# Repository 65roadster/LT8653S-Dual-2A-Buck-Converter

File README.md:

# LT8653S Dual 2A Buck Converter

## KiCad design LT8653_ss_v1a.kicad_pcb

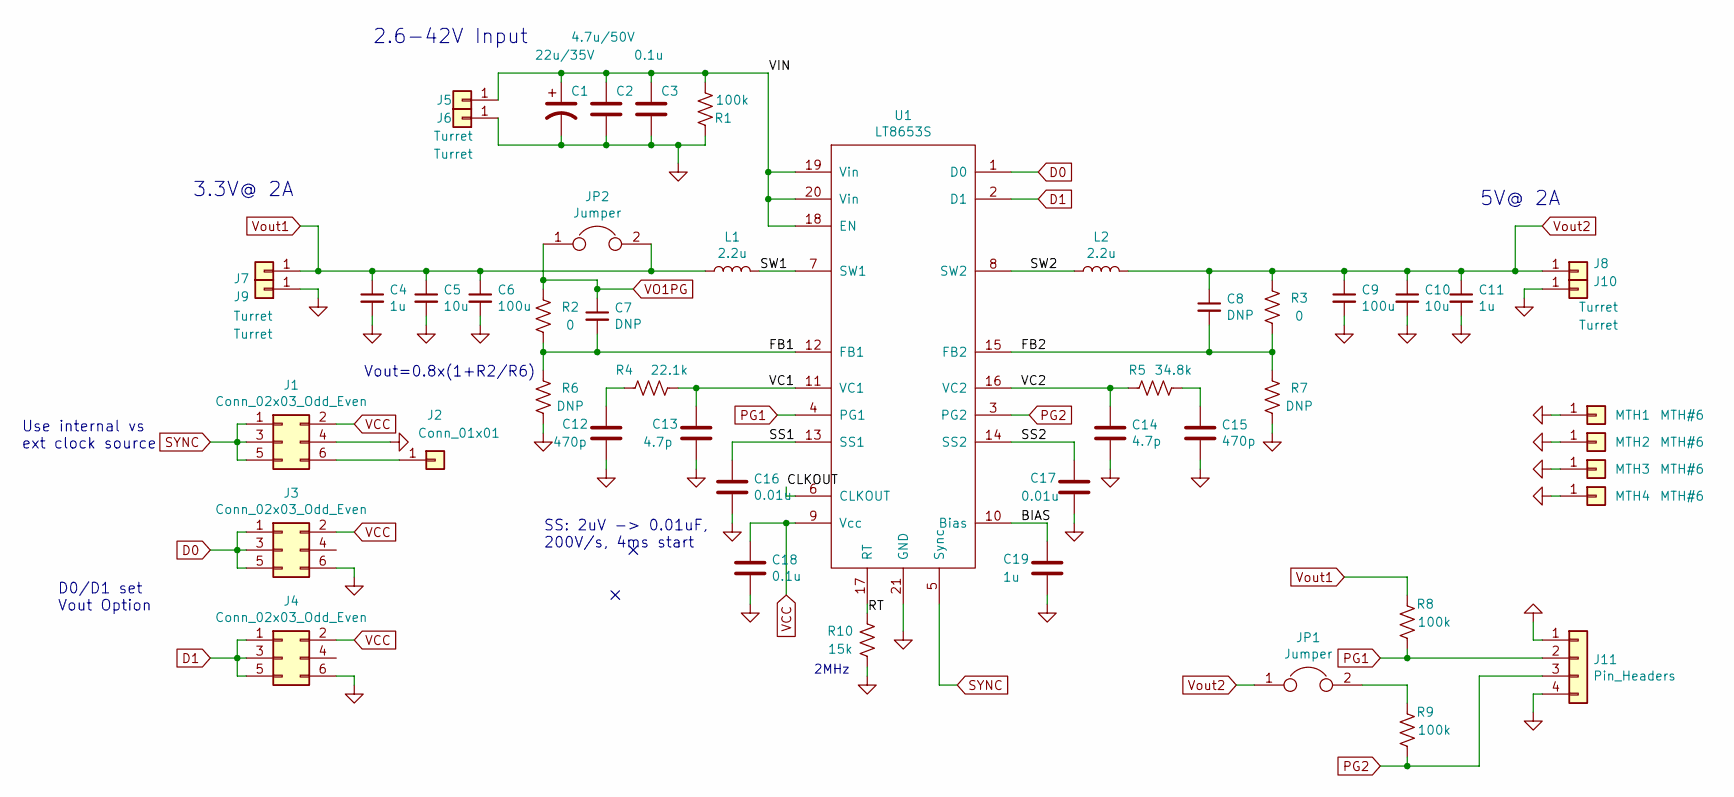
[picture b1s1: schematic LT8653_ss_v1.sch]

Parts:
C1: 22u/35V; CP_Elec_4x4.5
C2: 4.7u/50V; C_0603_HandSoldering
C3, C18: 0.1u; C_0603_HandSoldering
C4, C11, C19: 1u; C_0603_HandSoldering
C5, C10: 10u; C_0603_HandSoldering
C6, C9: 100u; C_1210_HandSoldering
C7, C8: DNP; C_0603_HandSoldering
C12, C15: 470p; C_0603_HandSoldering
C13, C14: 4.7p; C_0603_HandSoldering
C16, C17: 0.01u; C_0603_HandSoldering
J1, J3, J4: Conn_02x03_Odd_Even; Pin_Header_Straight_2x03_Pitch2.54mm
J2: Conn_01x01; Pin_Header_Straight_1x02_Pitch2.54mm
J5, J6, J7, J8, J9, J10: Turret; Pin-MILMAX_2501-2-00-80-00-00-07-0
J11: Pin_Headers; Pin_Header_Straight_1x04_Pitch2.54mm
JP1: Jumper; Jumper_0.3
JP2: Jumper; Jumper_0.6
L1, L2: 2.2u; Inductor_Coilcraft_XFL4020-222ME
MTH1, MTH2, MTH3, MTH4: MTH#6; Mount-Hole-#6
R1, R8, R9: 100k; R_0603_HandSoldering
R2, R3: 0; R_0603_HandSoldering
R4: 22.1k; R_0603_HandSoldering
R5: 34.8k; R_0603_HandSoldering
R6, R7: DNP; R_0603_HandSoldering
R10: 15k; R_0603_HandSoldering
U1: LT8653S; LinearTech-LT-LQFN-20-4mmx3mm

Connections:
/BIAS: C19.1, U1.10 (Bias)
/FB1: C7.2, R2.2, R6.1, U1.12 (FB1)
/FB2: C8.2, R3.2, R7.1, U1.15 (FB2)
/RT: R10.2, U1.17 (RT)
/SS1: C16.1, U1.13 (SS1)
/SS2: C17.1, U1.14 (SS2)
/SW1: L1.2, U1.7 (SW1)
/SW2: L2.1, U1.8 (SW2)
/VC1: C13.1, R4.2, U1.11 (VC1)
/VC2: C14.1, R5.1, U1.16 (VC2)
/VIN: C1.1, C2.1, C3.1, J5.1, R1.2, U1.18 (EN), U1.19 (Vin), U1.20 (Vin)
D0: J3.1, J3.3, J3.5, U1.1 (D0)
D1: J4.1, J4.3, J4.5, U1.2 (D1)
GND: C1.2, C2.2, C3.2, C4.2, C5.2, C6.2, C9.2, C10.2, C11.2, C12.2, C13.2, C14.2, C15.2, C16.2, C17.2, C18.2, C19.2, J1.4, J3.6, J4.6, J6.1, J9.1, J10.1, J11.1, J11.4, MTH1.1, MTH2.1, MTH3.1, MTH4.1, R1.1, R6.2, R7.2, R10.1, U1.21 (GND)
unnamed: C12.1, R4.1
unnamed: C15.1, R5.2
unnamed: J1.6, J2.1
unnamed: JP1.2, R9.1
PG1: J11.2, R8.2, U1.4 (PG1)
PG2: J11.3, R9.2, U1.3 (PG2)
SYNC: J1.1, J1.3, J1.5, U1.5 (Sync)
VCC: C18.1, J1.2, J3.2, J4.2, U1.9 (Vcc)
VO1PG: C7.1, JP2.1, R2.1
Vout1: C4.1, C5.1, C6.1, J7.1, JP2.2, L1.1, R8.1
Vout2: C8.1, C9.1, C10.1, C11.1, J8.1, JP1.1, L2.2, R3.1

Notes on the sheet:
2MHz
2.6-42V Input
SS: 2uV -> 0.01uF, 200V/s, 4ms start
Vout=0.8x(1+R2/R6)
3.3V@ 2A
5V@ 2A
D0/D1 set Vout Option
Use internal vs ext clock source

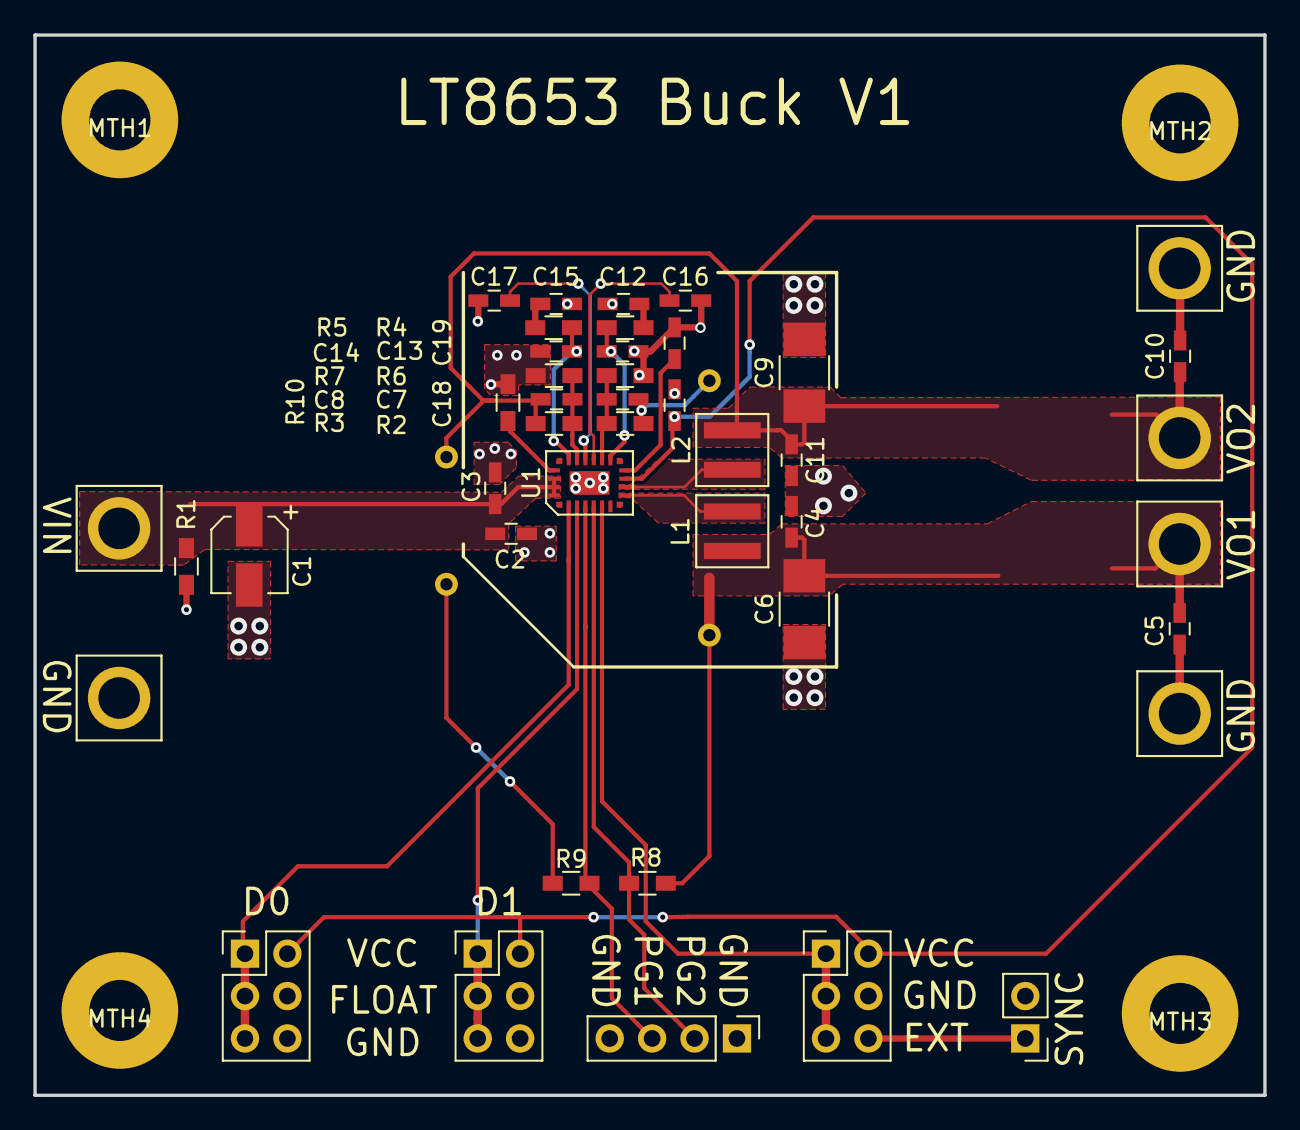
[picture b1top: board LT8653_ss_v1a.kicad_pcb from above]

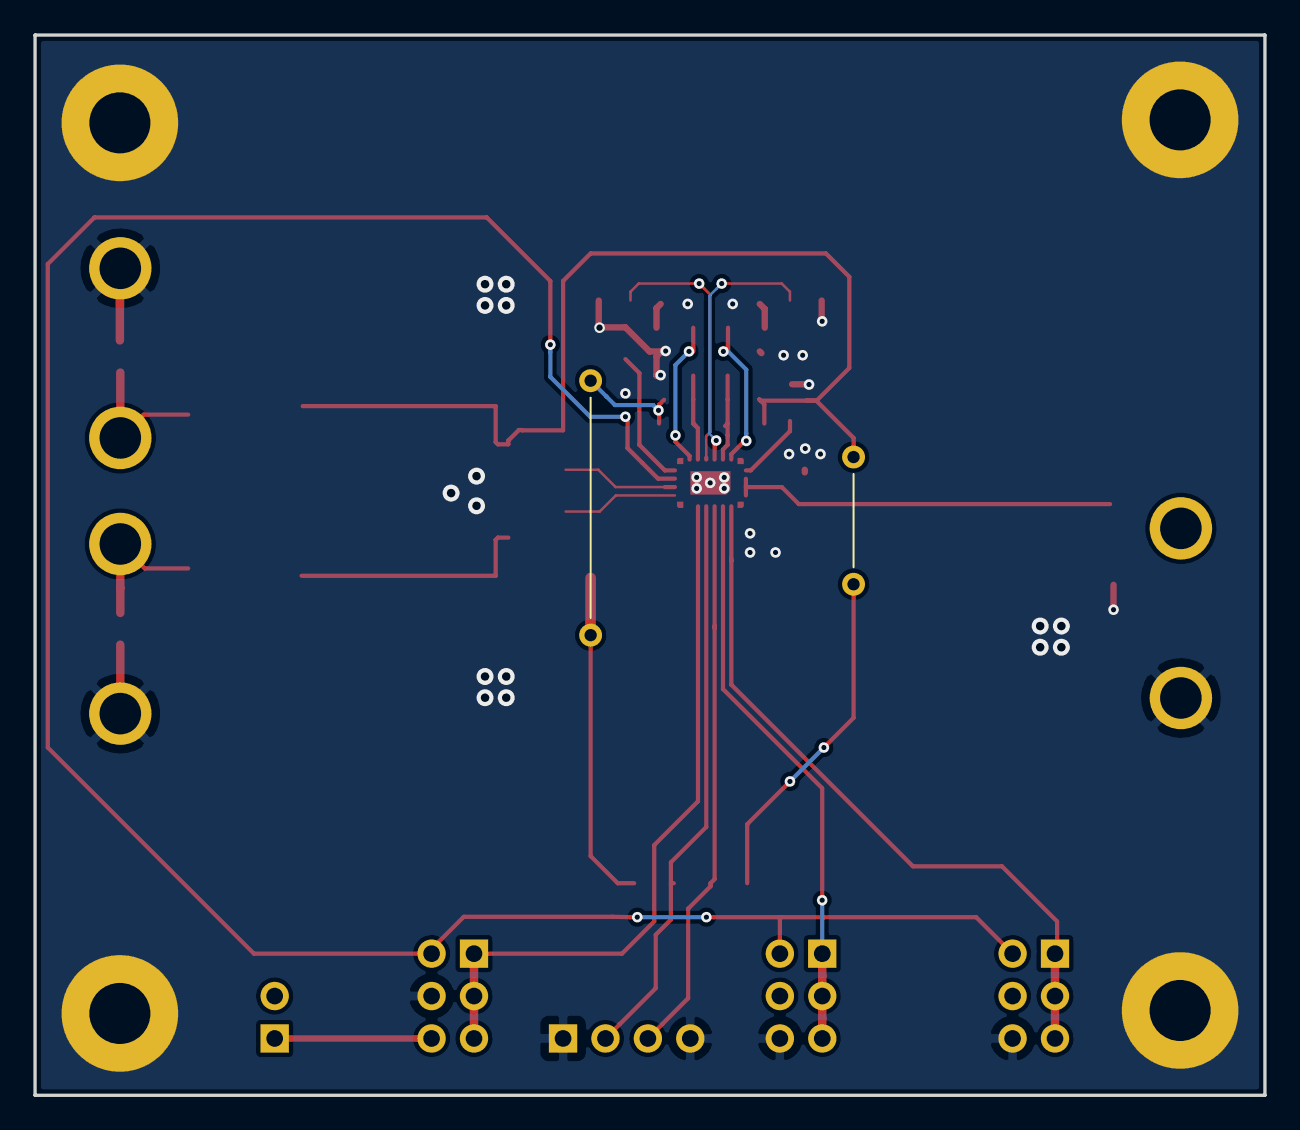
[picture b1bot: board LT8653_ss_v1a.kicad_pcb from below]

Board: 2 copper layers, 73.7 x 63.5 mm, 49 parts (2 on the bottom side), 25 nets.

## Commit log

2020-06-15 initial load
2020-06-15 Added comments to schematic
